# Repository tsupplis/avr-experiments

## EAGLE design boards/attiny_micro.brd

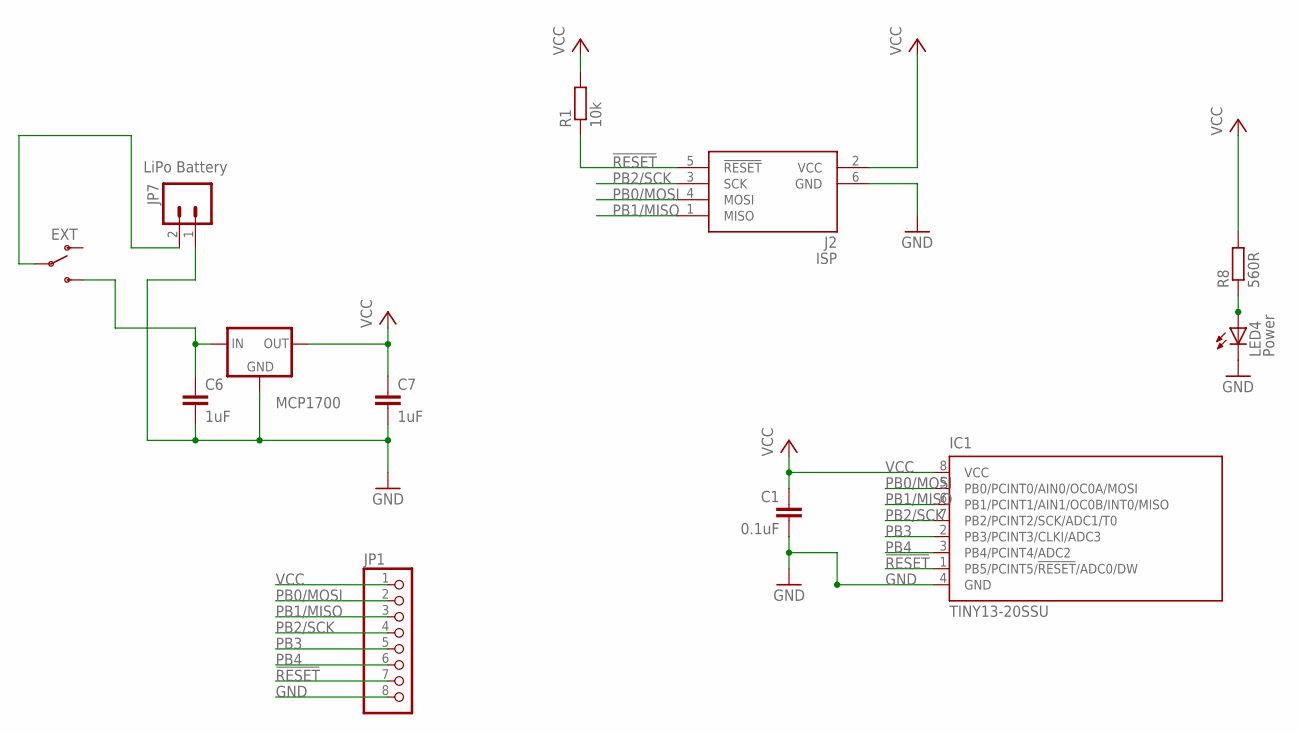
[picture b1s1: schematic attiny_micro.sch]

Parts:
C1: 0.1uF; C0805
C6, C7: 1uF; C0805
IC1: TINY13-20SSU; 8S1
J2: ISP; CON6P2R
JP1: PINHD-1X8; 1X08
JP7: LiPo Battery; JST-2-PTH
LED4: Power; CHIP-LED0805
MCP1700: MCP1700; SOT-23
ON: EXT; SWITCH-SPDT
R1: 10k; R0805
R8: 560R; R0805

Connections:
!RESET: IC1.1 (PB5/PCINT5/!RESET!/ADC0/DW), J2.5 (!RESET), JP1.7, R1.1
GND: C1.2, C6.2, C7.2, IC1.4 (GND), J2.6 (GND), JP1.8, JP7.1, LED4.C, MCP1700.1 (GND)
unnamed: LED4.A, R8.1
unnamed: JP7.2, ON.2
unnamed: C6.1, MCP1700.3 (IN), ON.3 (S)
PB0/MOSI: IC1.5 (PB0/PCINT0/AIN0/OC0A/MOSI), J2.4 (MOSI), JP1.2
PB1/MISO: IC1.6 (PB1/PCINT1/AIN1/OC0B/INT0/MISO), J2.1 (MISO), JP1.3
PB2/SCK: IC1.7 (PB2/PCINT2/SCK/ADC1/T0), J2.3 (SCK), JP1.4
PB3: IC1.2 (PB3/PCINT3/CLKI/ADC3), JP1.5
PB4: IC1.3 (PB4/PCINT4/ADC2), JP1.6
VCC: C1.1, C7.1, IC1.8 (VCC), J2.2 (VCC), JP1.1, MCP1700.2 (OUT), R1.2, R8.2

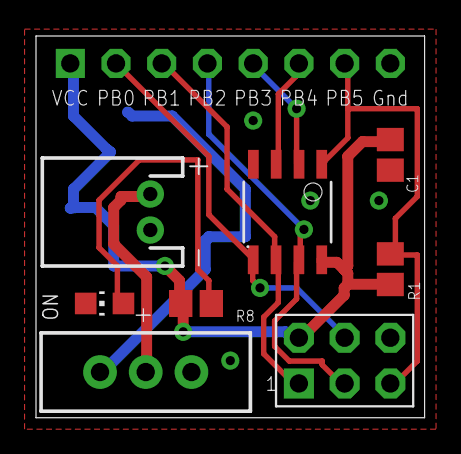
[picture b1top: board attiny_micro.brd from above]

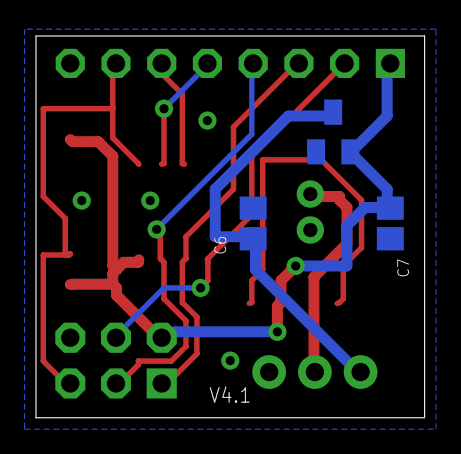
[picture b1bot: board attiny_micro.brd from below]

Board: 2 copper layers, 21.6 x 21.2 mm, 12 parts (3 on the bottom side), 11 nets.

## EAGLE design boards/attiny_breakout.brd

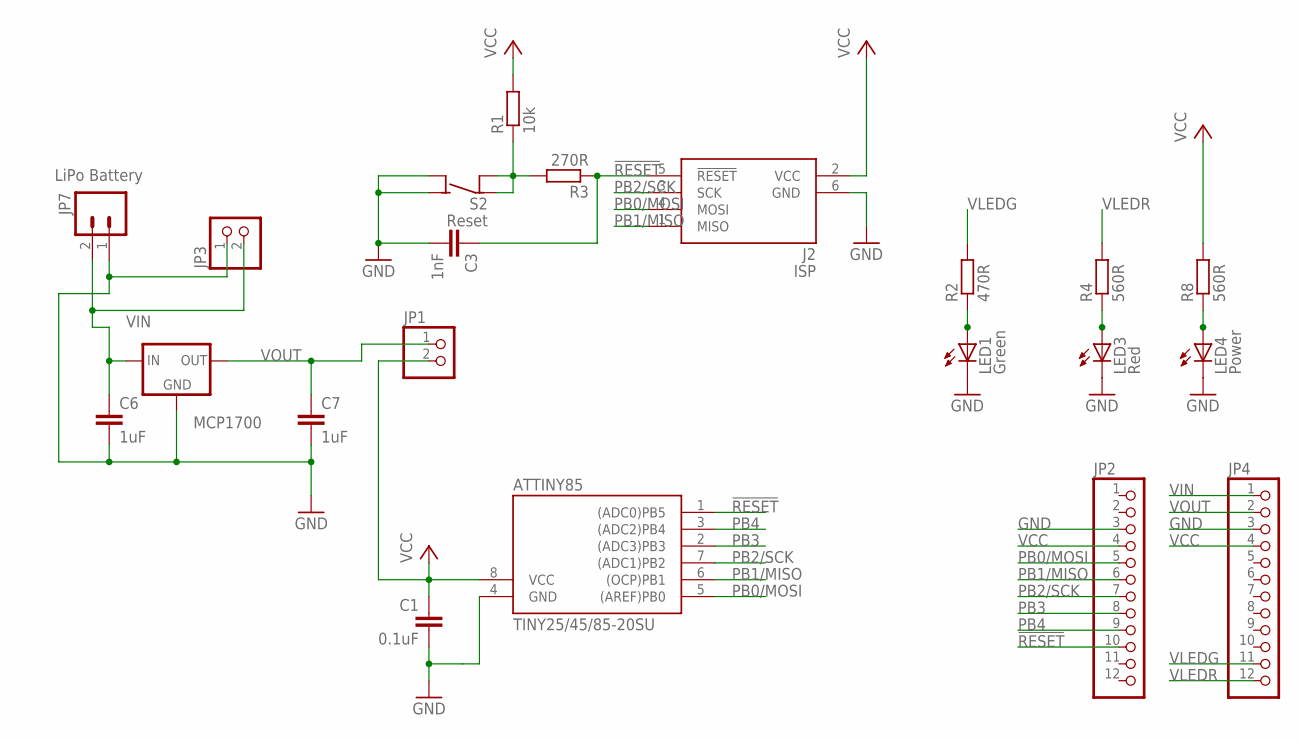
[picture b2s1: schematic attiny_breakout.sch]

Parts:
ATTINY85: TINY25/45/85-20SU; SOIC8
C1: 0.1uF; C0805
C3: 1nF; C0805
C6, C7: 1uF; C0805
J2: ISP; CON6P2R
JP1, JP3: PINHD-1X2; 1X02
JP2, JP4: PINHD-1X12; 1X12
JP7: LiPo Battery; JST-2-PTH
LED1: Green; CHIP-LED0805
LED3: Red; CHIP-LED0805
LED4: Power; CHIP-LED0805
MCP1700: MCP1700; SOT-23
R1: 10k; R0805
R2: 470R; R0805
R3: 270R; R0805
R4, R8: 560R; R0805
S2: Reset; 6MMTACTILE_4PIN

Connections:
!RESET: ATTINY85.1 ((ADC0)PB5), C3.1, J2.5 (!RESET), JP2.10, R3.1
GND: ATTINY85.4 (GND), C1.2, C3.2, C6.2, C7.2, J2.6 (GND), JP2.3, JP3.1, JP4.3, JP7.1, LED1.C, LED3.C, LED4.C, MCP1700.1 (GND), S2.A1 (NO), S2.A2 (NO)
unnamed: LED3.A, R4.1
unnamed: LED4.A, R8.1
unnamed: R1.1, R3.2, S2.B1 (COM), S2.B2 (COM)
unnamed: LED1.A, R2.1
PB0/MOSI: ATTINY85.5 ((AREF)PB0), J2.4 (MOSI), JP2.5
PB1/MISO: ATTINY85.6 ((OCP)PB1), J2.1 (MISO), JP2.6
PB2/SCK: ATTINY85.7 ((ADC1)PB2), J2.3 (SCK), JP2.7
PB3: ATTINY85.2 ((ADC3)PB3), JP2.8
PB4: ATTINY85.3 ((ADC2)PB4), JP2.9
VCC: ATTINY85.8 (VCC), C1.1, J2.2 (VCC), JP1.2, JP2.4, JP4.4, R1.2, R8.2
VIN: C6.1, JP3.2, JP4.1, JP7.2, MCP1700.3 (IN)
VLEDG: JP4.11, R2.2
VLEDR: JP4.12, R4.2
VOUT: C7.1, JP1.1, JP4.2, MCP1700.2 (OUT)

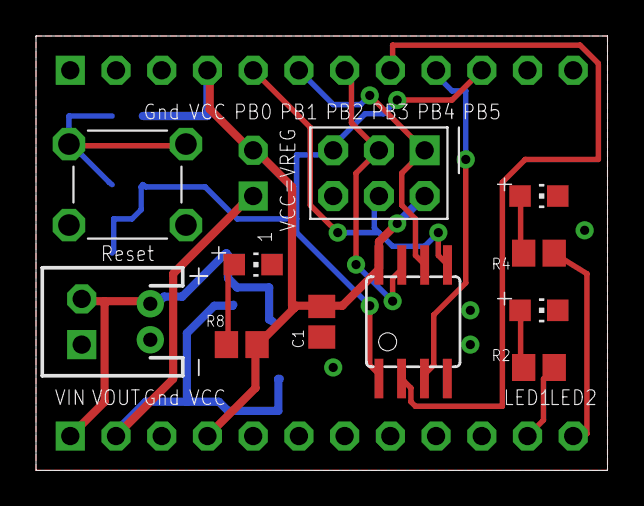
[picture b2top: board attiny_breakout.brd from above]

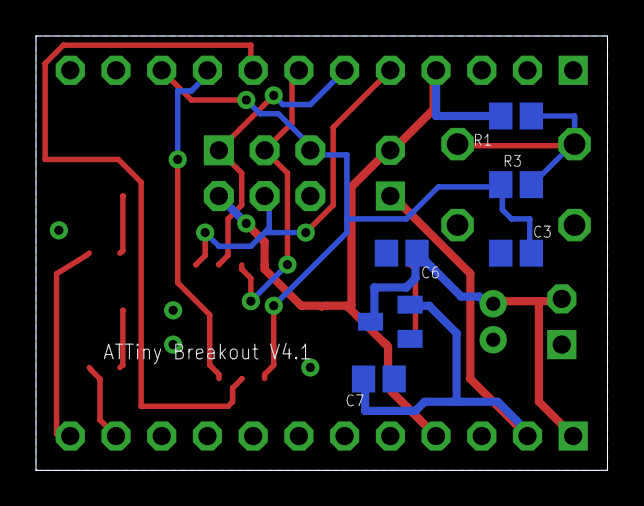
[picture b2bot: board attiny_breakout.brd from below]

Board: 2 copper layers, 31.8 x 24.1 mm, 21 parts (6 on the bottom side), 16 nets.

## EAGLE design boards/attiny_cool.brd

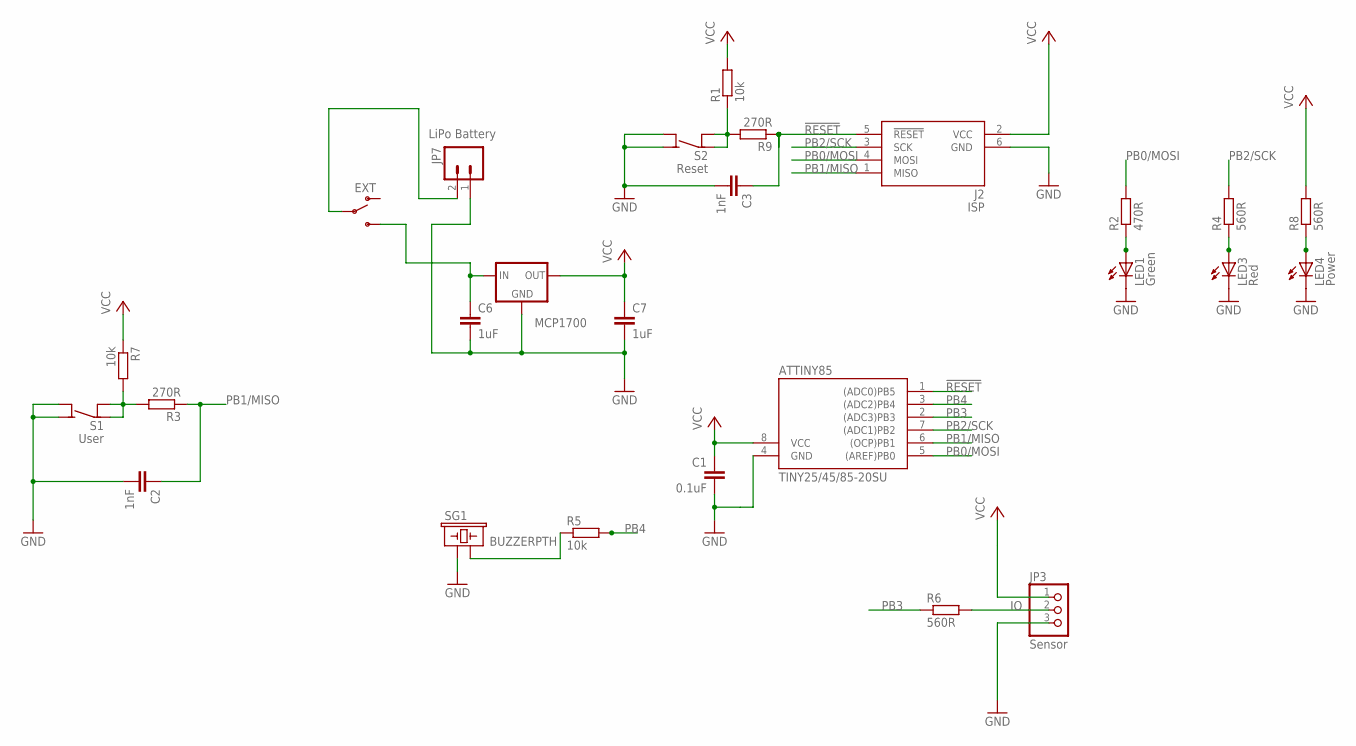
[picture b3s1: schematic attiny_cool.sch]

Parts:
ATTINY85: TINY25/45/85-20SU; SOIC8
C1: 0.1uF; C0805
C2, C3: 1nF; C0805
C6, C7: 1uF; C0805
J2: ISP; CON6P2R
JP3: Sensor; 1X03
JP7: LiPo Battery; JST-2-PTH
LED1: Green; CHIPLED_1206
LED3: Red; CHIPLED_1206
LED4: Power; CHIPLED_1206
MCP1700: MCP1700; SOT-23
ON: EXT; SWITCH-SPDT
R1, R5, R7: 10k; R0805
R2: 470R; R0805
R3, R9: 270R; R0805
R4, R6, R8: 560R; R0805
S1: User; 6MMTACTILE_4PIN
S2: Reset; 6MMTACTILE_4PIN
SG1: BUZZERPTH; BUZZER-12MM

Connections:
!RESET: ATTINY85.1 ((ADC0)PB5), C3.1, J2.5 (!RESET), R9.1
GND: ATTINY85.4 (GND), C1.2, C2.2, C3.2, C6.2, C7.2, J2.6 (GND), JP3.3, JP7.1, LED1.C, LED3.C, LED4.C, MCP1700.1 (GND), S1.A1 (NO), S1.A2 (NO), S2.A1 (NO), S2.A2 (NO), SG1.+ (1)
IO: JP3.2, R6.2
unnamed: LED3.A, R4.1
unnamed: LED4.A, R8.1
unnamed: JP7.2, ON.2
unnamed: LED1.A, R2.1
unnamed: R3.2, R7.2, S1.B1 (COM), S1.B2 (COM)
unnamed: R5.1, SG1.- (2)
unnamed: R1.1, R9.2, S2.B1 (COM), S2.B2 (COM)
unnamed: C6.1, MCP1700.3 (IN), ON.3 (S)
PB0/MOSI: ATTINY85.5 ((AREF)PB0), J2.4 (MOSI), R2.2
PB1/MISO: ATTINY85.6 ((OCP)PB1), C2.1, J2.1 (MISO), R3.1
PB2/SCK: ATTINY85.7 ((ADC1)PB2), J2.3 (SCK), R4.2
PB3: ATTINY85.2 ((ADC3)PB3), R6.1
PB4: ATTINY85.3 ((ADC2)PB4), R5.2
VCC: ATTINY85.8 (VCC), C1.1, C7.1, J2.2 (VCC), JP3.1, MCP1700.2 (OUT), R1.2, R7.1, R8.2

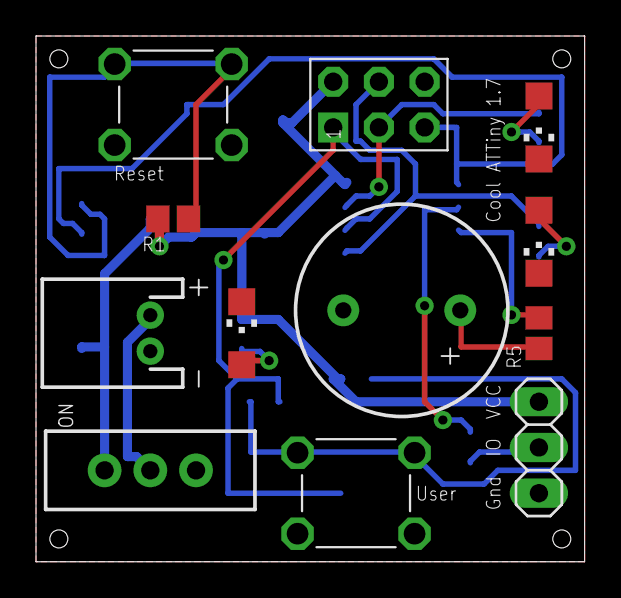
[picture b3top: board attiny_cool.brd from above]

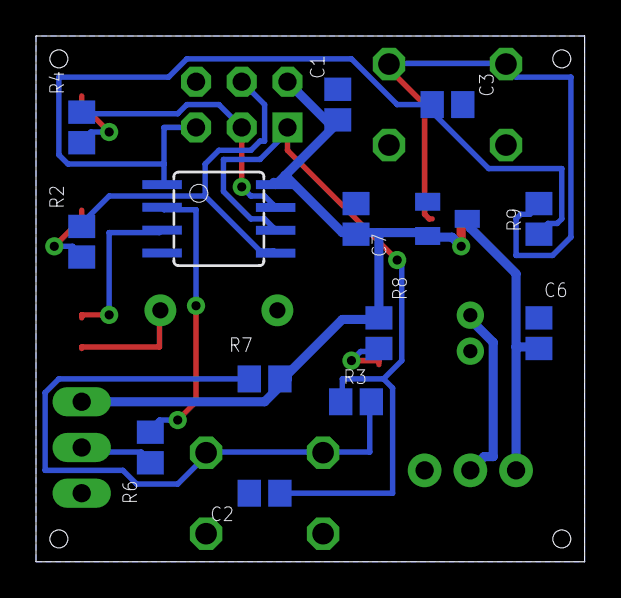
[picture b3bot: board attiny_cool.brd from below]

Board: 2 copper layers, 30.5 x 29.2 mm, 26 parts (14 on the bottom side), 17 nets.

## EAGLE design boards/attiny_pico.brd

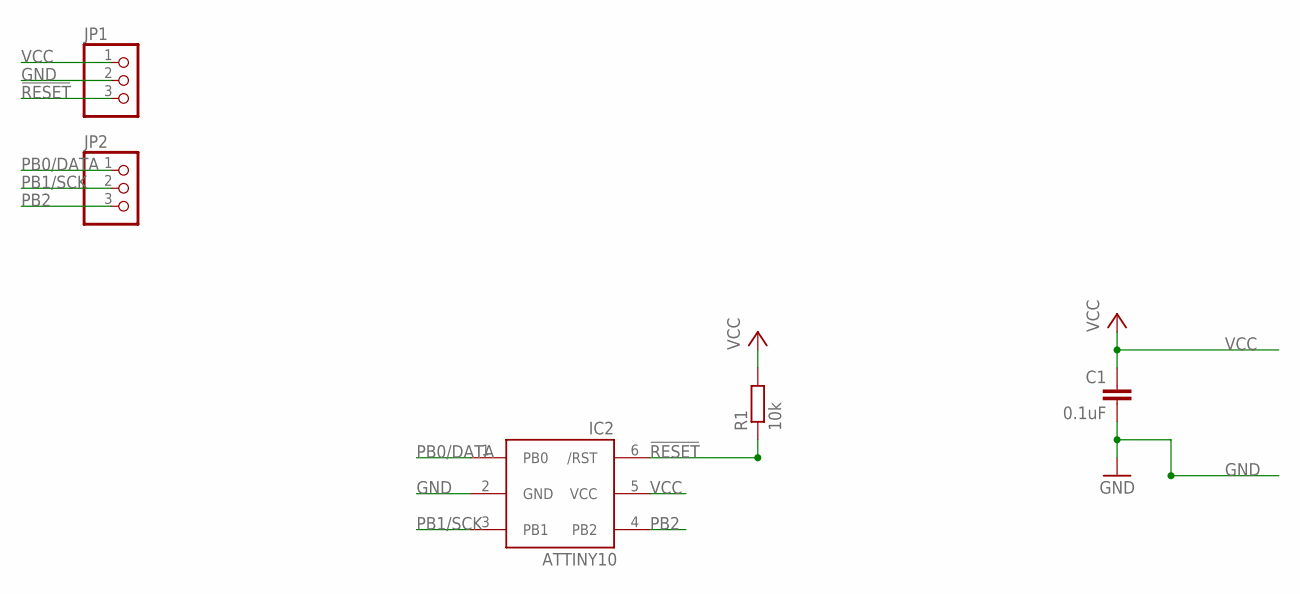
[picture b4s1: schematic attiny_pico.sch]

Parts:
C1: 0.1uF; C0805
IC2: ATTINY10; SOT23-6
JP1, JP2: PINHD-1X3; 1X03
R1: 10k; R0805

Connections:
!RESET: IC2.6 (/RST), JP1.3, R1.1
GND: C1.2, IC2.2 (GND), JP1.2
PB0/DATA: IC2.1 (PB0), JP2.1
PB1/SCK: IC2.3 (PB1), JP2.2
PB2: IC2.4 (PB2), JP2.3
VCC: C1.1, IC2.5 (VCC), JP1.1, R1.2

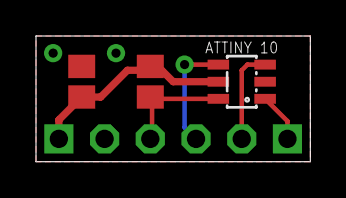
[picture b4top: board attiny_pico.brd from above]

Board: 2 copper layers, 15.2 x 7.0 mm, 5 parts (0 on the bottom side), 6 nets.

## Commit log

2016-04-05 Initial Content

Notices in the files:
parts and their libraries:
SparkFun: Licensing: CC v3.0 Share-Alike You are welcome to use this library for commercial purposes.
